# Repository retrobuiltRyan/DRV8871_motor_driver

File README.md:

# DRV8871_motor_driver
PCB for DRV8871: a basic DC motor driver for small  to maybe medium brushed motors. https://www.ti.com/lit/ds/symlink/drv8871.pdf

### Quick Specs
- H-Bridge Motor Driver  
- Drives one DC motor, one winding of a stepper motor, or other loads  
- Wide operating voltage: **6.5 V to 45 V**  
- **565 mΩ** typical RDS(on) (HS + LS)  
- **3.6 A** peak current drive  
- PWM control interface  
- Current regulation without a sense resistor  

##BoM
### Bill of Materials (BOM)

| Reference | Value      | Qty | Digi-Key P/N                 |
|-----------|------------|-----|------------------------------|
| C1        | 47µF 35V   | 1   | PCE5014CT-ND                 |
| C2        | 0.1µF 35V  | 1   | 399-C1206C104M6RACTUCT-ND    |
| D2        | LED        | 1   | 732-4989-1-ND                |
| D3, D4    | SMF15A     | 2   | SMF15A-E3-08CT-ND            |
| R1        | 32k        | 1   | 2019-RN73H2BTTD3202F100CT-ND |
| R3        | 1k         | 1   | 311-1.00KFRCT-ND             |
| U1        | DRV8871DDA | 1   | 296-43024-1-ND               |

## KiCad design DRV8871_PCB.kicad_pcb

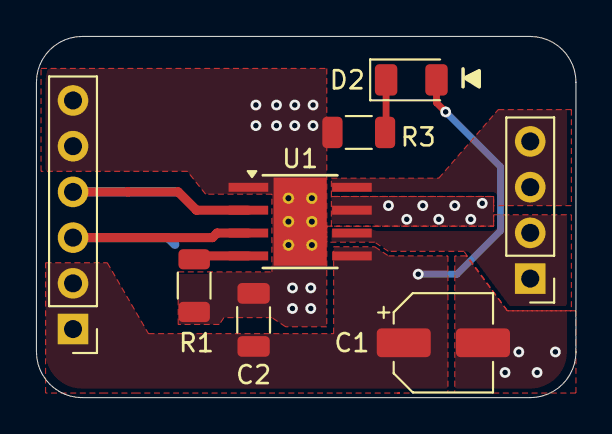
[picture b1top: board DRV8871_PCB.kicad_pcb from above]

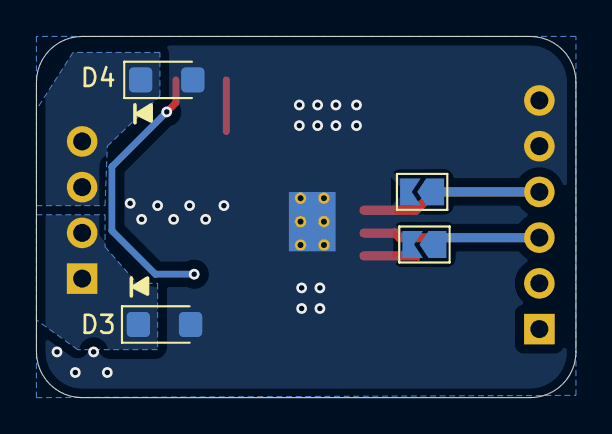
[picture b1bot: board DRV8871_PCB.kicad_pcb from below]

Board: 2 copper layers, 30.0 x 20.1 mm, 12 parts (4 on the bottom side), 8 nets.

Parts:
C1: 0.1uF 50V; CP_Elec_5x5.3
C2: 47uF 50V; C_1206_3216Metric
D2: LED; LED_1206_3216Metric
D3, D4: SMF15A; D_SMF
J4: PINHD_1x4_Male; PinHeader_1x04_P2.54mm_Vertical
J6: PINHD_1x6_Male; PinHeader_1x06_P2.54mm_Vertical
JP1, JP2: SolderJumper_2_Open; SolderJumper-2_P1.3mm_Open_TrianglePad1.0x1.5mm
R1: 32k; R_1206_3216Metric
R3: 1k; R_1206_3216Metric
U1: DRV8871DDA; Texas_HTSOP-8-1EP_3.9x4.9mm_P1.27mm_EP2.95x4.9mm_Mask2.4x3.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

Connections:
/DRV_C1: J6.3, JP2.1 (A), U1.3 (IN1)
/DRV_C2: J6.4, JP1.1 (A), U1.2 (IN2)
/VM: C1.1, C2.1, D2.2 (A), J6.1, J6.2, U1.5 (VM)
GND: C1.2, C2.2, D3.2 (A2), D4.2 (A2), J6.5, J6.6, JP1.2 (B), JP2.2 (B), R1.2, R3.2, U1.1 (GND), U1.7 (GND), U1.9 (GND)
unnamed: D2.1 (K), R3.1
unnamed: D3.1 (A1), J4.1, J4.2, U1.6 (OUT1)
unnamed: D4.1 (A1), J4.3, J4.4, U1.8 (OUT2)
unnamed: R1.1, U1.4 (ILIM)

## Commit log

2025-08-27 KiCAD design files
2025-08-27 Gerbers
    (zip file is all the gerbers together)
2025-08-27 schematic (PDF)

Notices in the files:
DRV8871_PCB.kicad_pcb:
(c)2024 Ryan Bates
